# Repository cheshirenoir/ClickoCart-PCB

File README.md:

# ClickoCart-PCB
A multicart for the Colecovision
# THIS IS CURRENTLY NOT WORKING DO NOT USE
It's supposed to be a super cheap Colecovision cart capable of playing most of the available ROMs from one cart using DIP switches rather than code to choose the ROM.

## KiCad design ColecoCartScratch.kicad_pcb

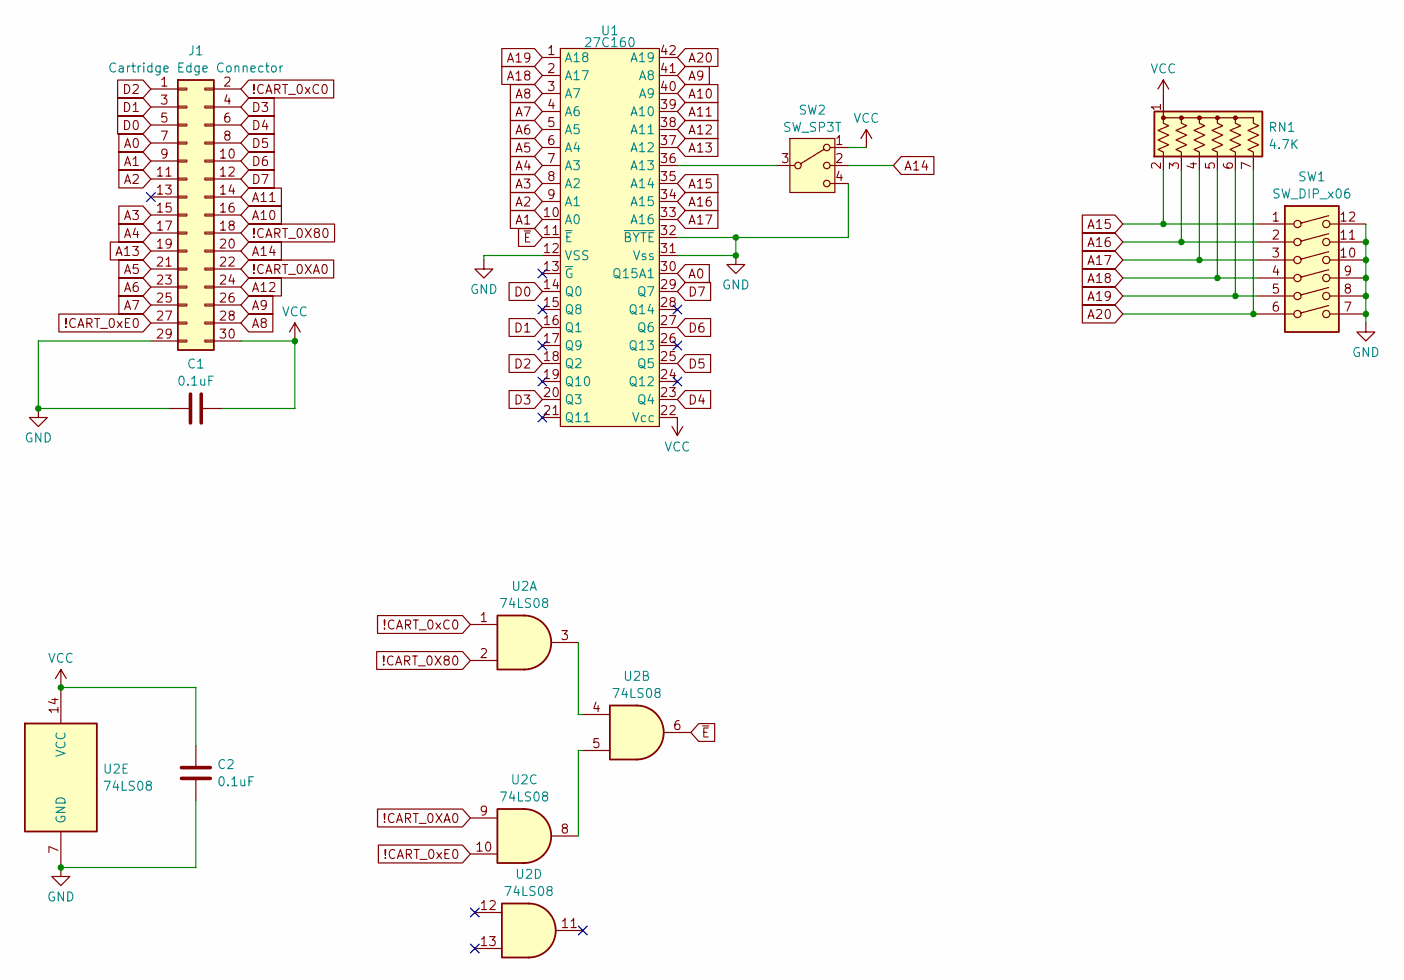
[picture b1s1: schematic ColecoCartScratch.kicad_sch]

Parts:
C1, C2: 0.1uF; C_Disc_D4.3mm_W1.9mm_P5.00mm
J1: Cartridge Edge Connector; 30 Way Edge Connector
RN1: 4.7K; R_Array_SIP7
SW1: SW_DIP_x06; DIP-12_W7.62mm_LongPads
SW2: SW_SP3T; PinHeader_1x04_P2.54mm_Vertical
U1: 27C160; DIP-42_W15.24mm_Socket_LongPads
U2: 74LS08; DIP-14_W7.62mm_LongPads

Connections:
!CART_0X80: J1.18, U2.2
!CART_0XA0: J1.22, U2.9
!CART_0xC0: J1.2, U2.1
!CART_0xE0: J1.27, U2.10
A0: J1.7, U1.30 (Q15A1)
A1: J1.9, U1.10 (A0)
A2: J1.11, U1.9 (A1)
A3: J1.15, U1.8 (A2)
A4: J1.17, U1.7 (A3)
A5: J1.21, U1.6 (A4)
A6: J1.23, U1.5 (A5)
A7: J1.25, U1.4 (A6)
A8: J1.28, U1.3 (A7)
A9: J1.26, U1.41 (A8)
A10: J1.16, U1.40 (A9)
A11: J1.14, U1.39 (A10)
A12: J1.24, U1.38 (A11)
A13: J1.19, U1.37 (A12)
A14: J1.20, SW2.2
A15: RN1.2 (R1), SW1.1, U1.35 (A14)
A16: RN1.3 (R2), SW1.2, U1.34 (A15)
A17: RN1.4 (R3), SW1.3, U1.33 (A16)
A18: RN1.5 (R4), SW1.4, U1.2 (A17)
A19: RN1.6 (R5), SW1.5, U1.1 (A18)
A20: RN1.7 (R6), SW1.6, U1.42 (A19)
D0: J1.5, U1.14 (Q0)
D1: J1.3, U1.16 (Q1)
D2: J1.1, U1.18 (Q2)
D3: J1.4, U1.20 (Q3)
D4: J1.6, U1.23 (Q4)
D5: J1.8, U1.25 (Q5)
D6: J1.10, U1.27 (Q6)
D7: J1.12, U1.29 (Q7)
GND: C1.2, C2.2, J1.29, SW1.7, SW1.8, SW1.9, SW1.10, SW1.11, SW1.12, SW2.4, U1.12 (VSS), U1.31 (Vss), U1.32 (~BYTE), U2.7 (GND)
unnamed: SW2.3, U1.36 (A13)
unnamed: U2.3, U2.4
unnamed: U2.5, U2.8
VCC: C1.1, C2.1, J1.30, RN1.1 (common), SW2.1, U1.22 (Vcc), U2.14 (VCC)
~E: U1.11 (~E), U2.6

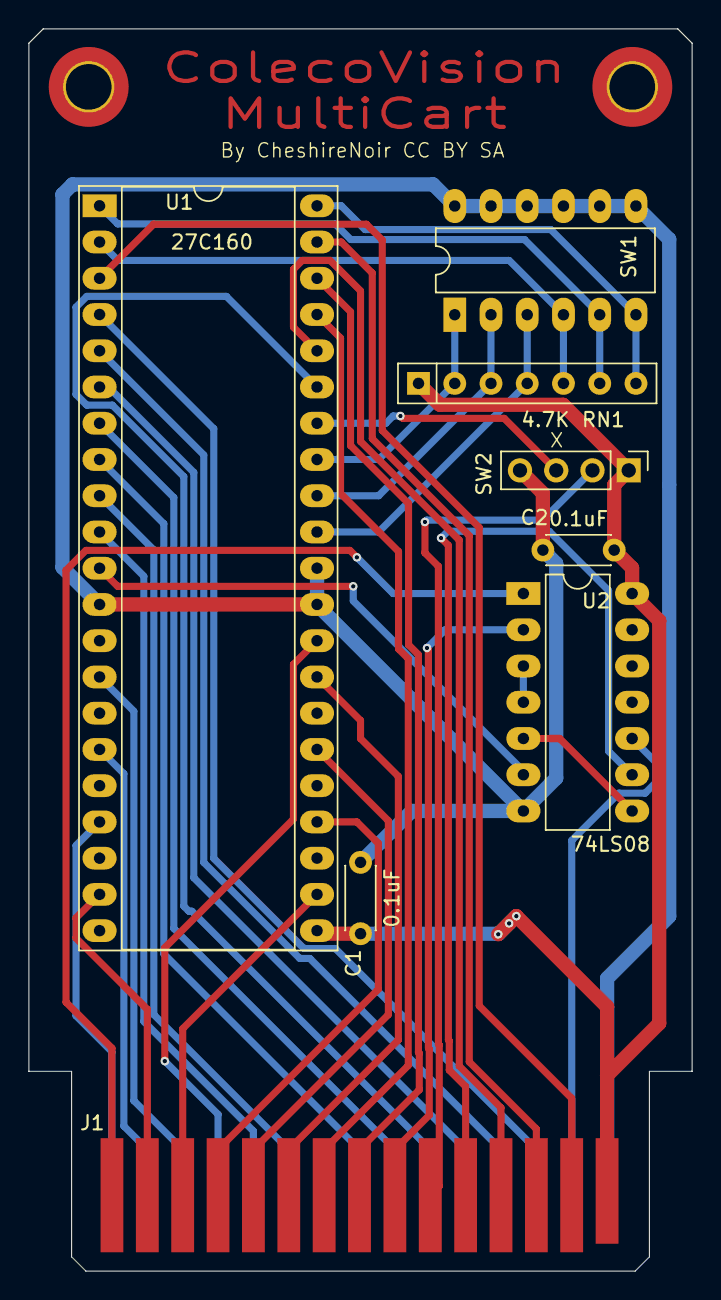
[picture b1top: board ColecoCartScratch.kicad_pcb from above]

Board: 2 copper layers, 46.5 x 87.1 mm, 10 parts (0 on the bottom side), 39 nets.

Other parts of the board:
MH: MountingHole_3.2mm_M3_DIN965_Pad_TopBottom
MH#2: MountingHole_3.2mm_M3_DIN965_Pad_TopBottom

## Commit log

2024-11-07 Add files via upload
    The case to go with the cart

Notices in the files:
ColecoCartScratch.kicad_pcb:
By CheshireNoir CC BY SA
